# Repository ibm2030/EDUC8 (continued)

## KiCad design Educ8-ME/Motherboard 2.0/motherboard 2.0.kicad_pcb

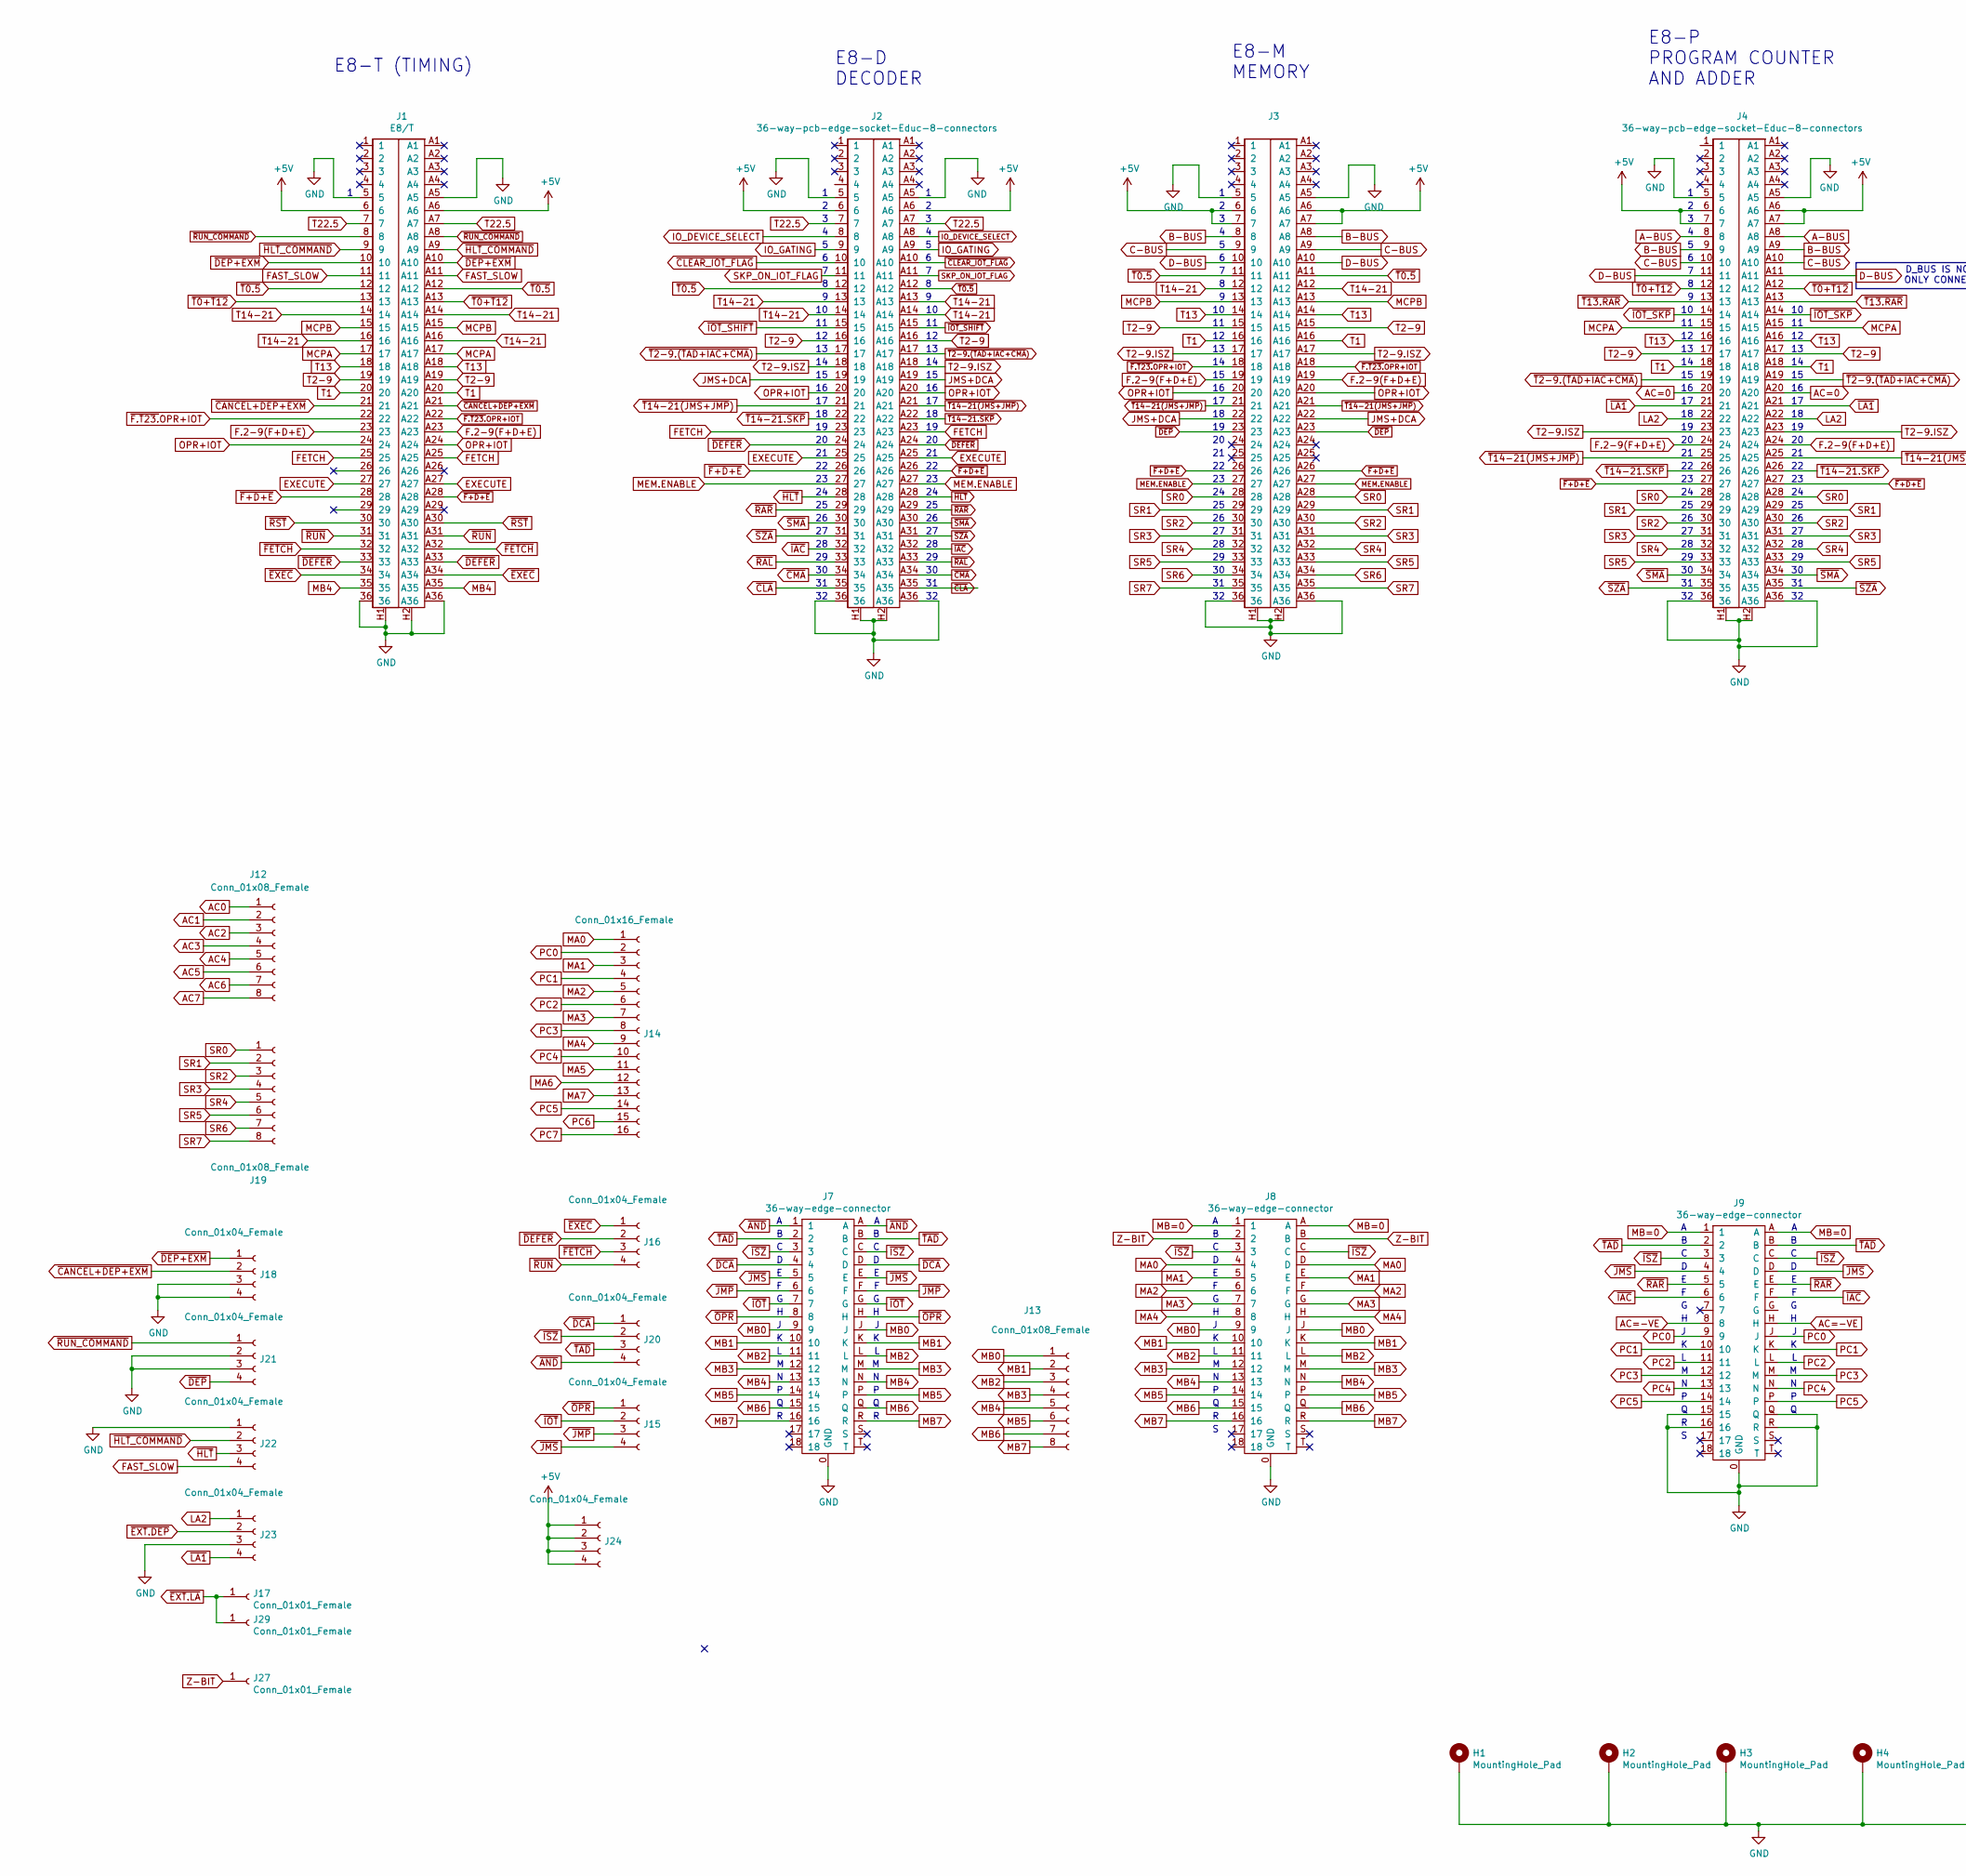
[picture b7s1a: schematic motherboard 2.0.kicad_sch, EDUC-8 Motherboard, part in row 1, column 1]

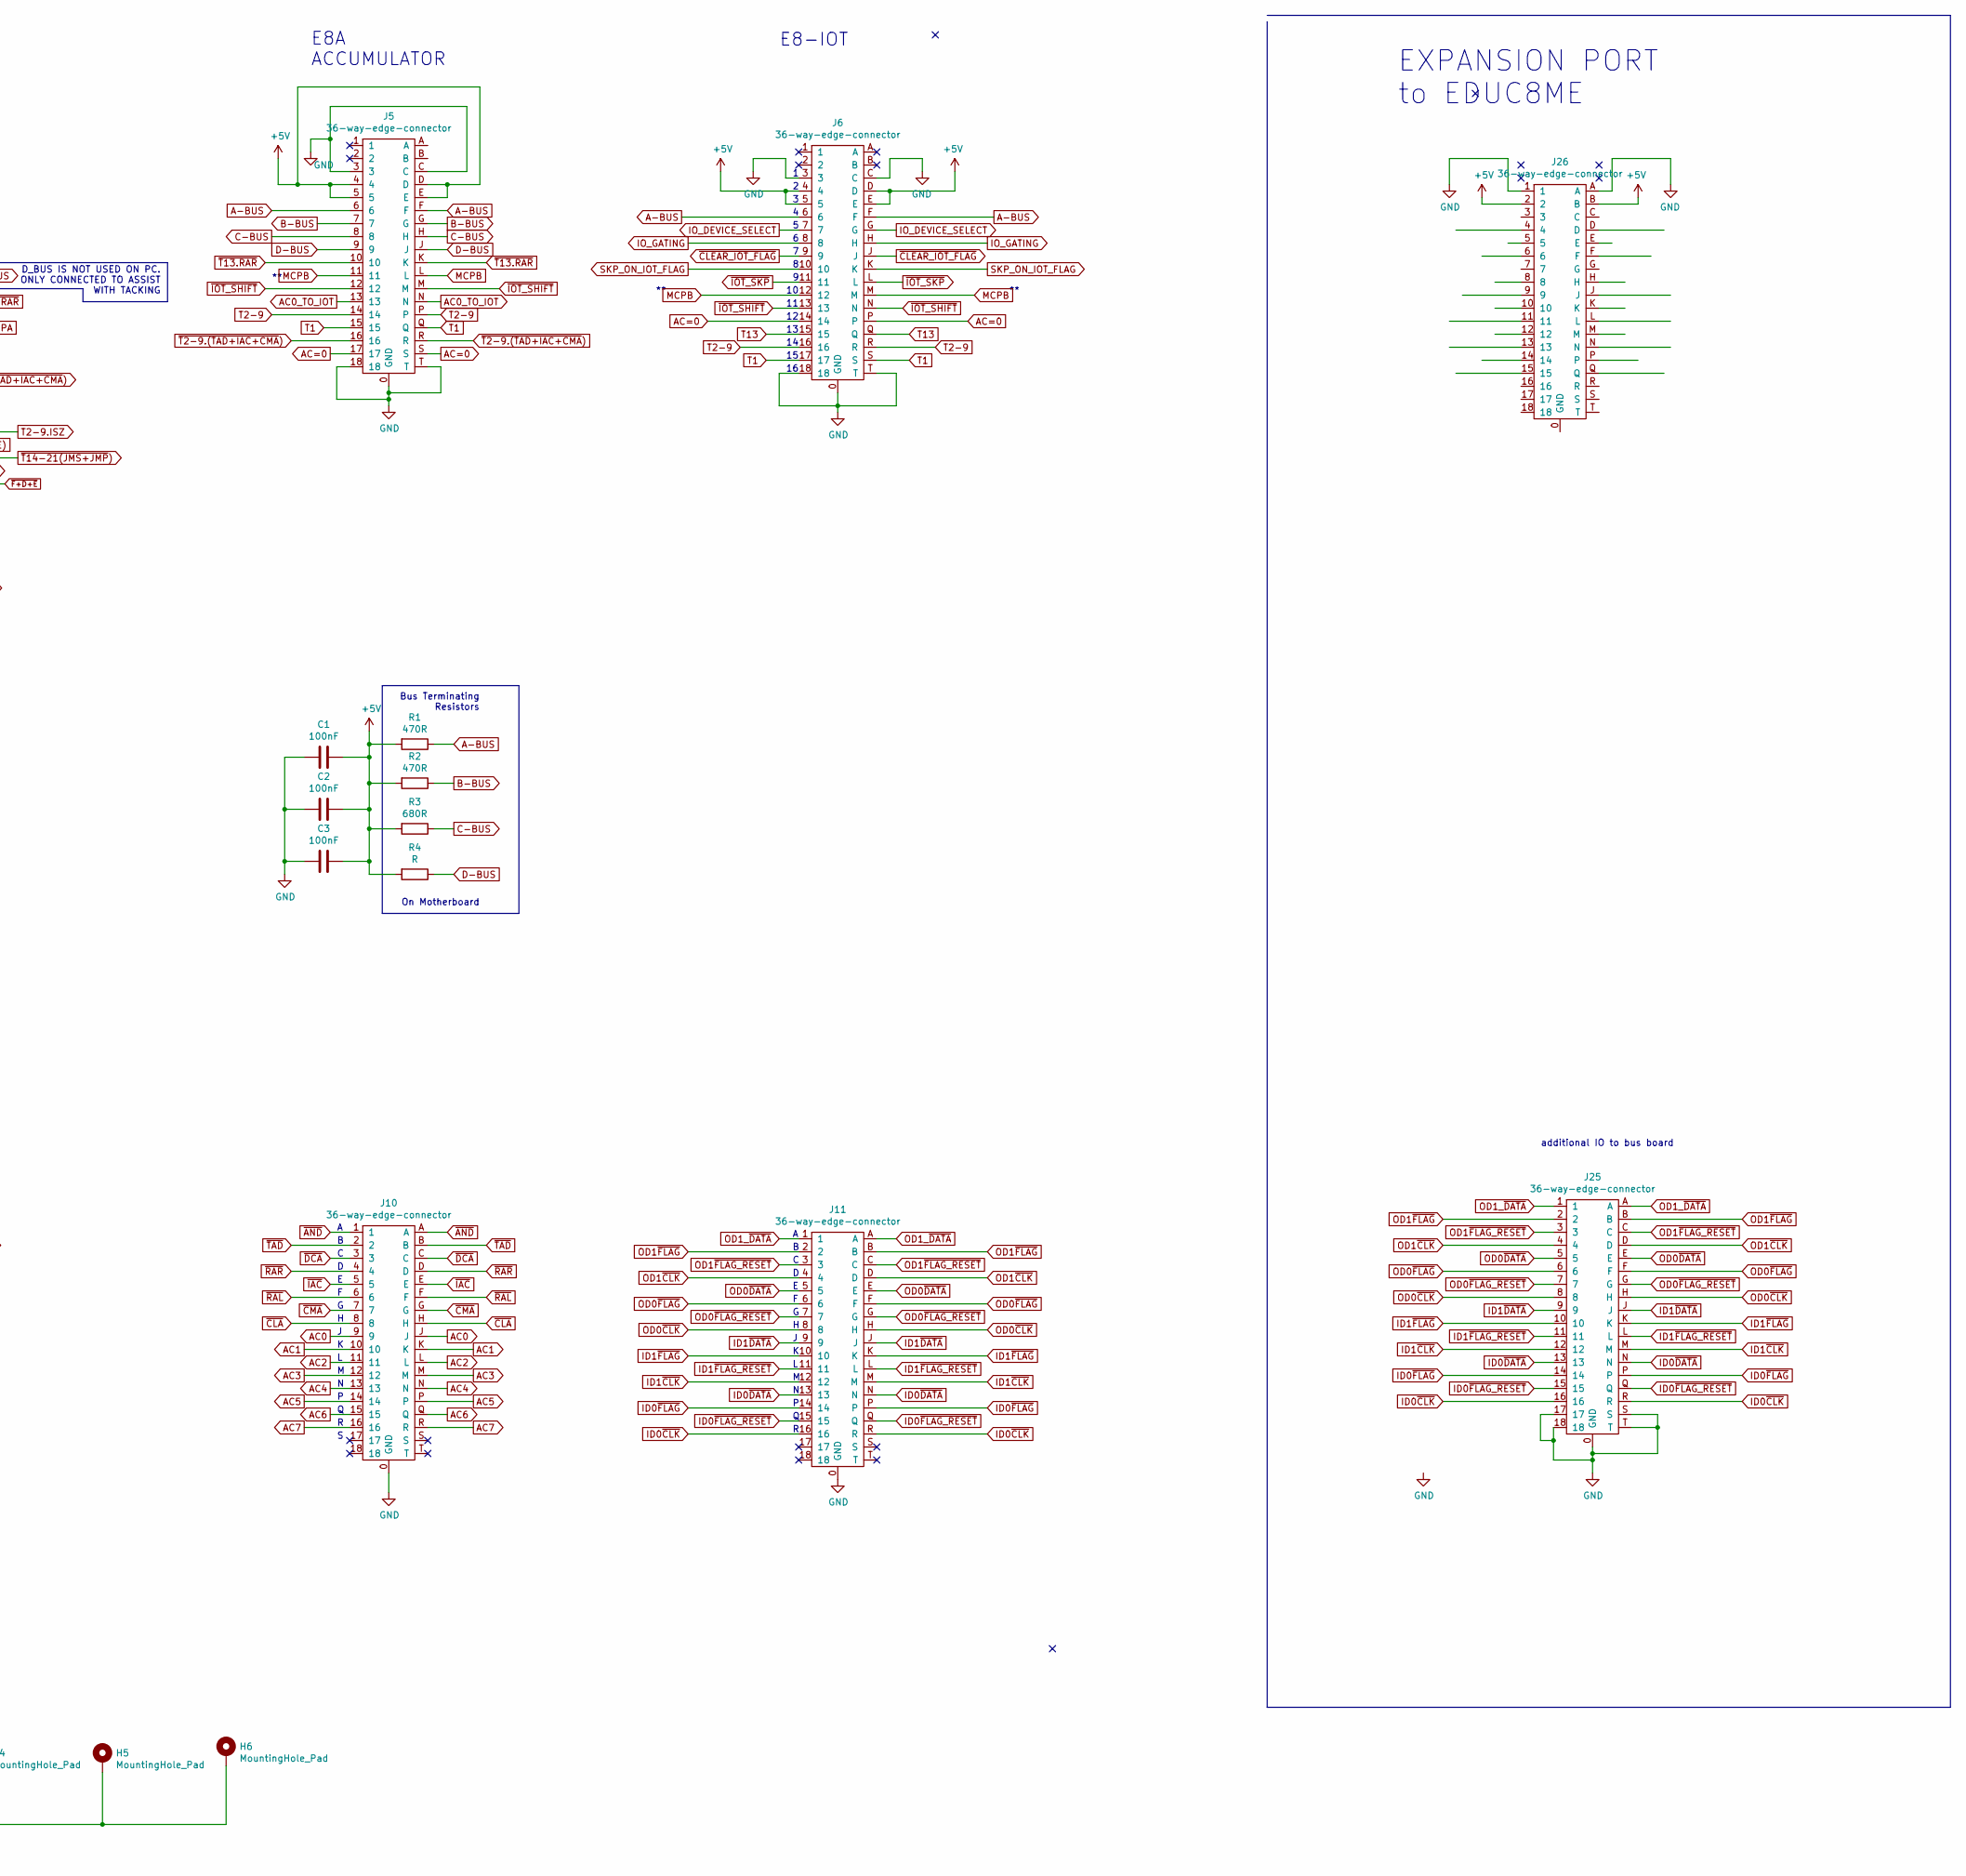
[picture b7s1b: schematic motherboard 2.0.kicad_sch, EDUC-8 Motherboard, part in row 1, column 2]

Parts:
C1, C2, C3: 100nF; C_Disc_D8.0mm_W5.0mm_P7.50mm
H1, H2, H3, H4, H5, H6: MountingHole_Pad; MountingHole_3.2mm_M3_Pad_Via
J1: E8/T; 72_way_3.96mm_card_edge_socket
J2, J4: 36-way-pcb-edge-socket-Educ-8-connectors; 72_way_3.96mm_card_edge_socket
J3: (no value)
J5, J6, J7, J8, J9, J10, J11, J25, J26: 36-way-edge-connector; 36_way_3.96mm_card_edge_socket
J12, J13, J19: Conn_01x08_Female; PinHeader_1x08_P2.54mm_Vertical
J14: Conn_01x16_Female; PinHeader_1x16_P2.54mm_Vertical
J15, J16, J18, J20, J21, J22, J23, J24: Conn_01x04_Female; PinHeader_1x04_P2.54mm_Vertical
J17, J27, J29: Conn_01x01_Female; PinHeader_1x01_P2.54mm_Vertical
R1, R2: 470R; R_Axial_DIN0207_L6.3mm_D2.5mm_P10.16mm_Horizontal
R3: 680R; R_Axial_DIN0207_L6.3mm_D2.5mm_P10.16mm_Horizontal
R4: R; R_Axial_DIN0207_L6.3mm_D2.5mm_P10.16mm_Horizontal

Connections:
+5V: C1.1, C2.1, C3.1, J1.6, J1.A6, J2.6, J2.A6, J3.6, J3.7, J3.A6, J3.A7, J4.6, J4.7, J4.A6, J4.A7, J5.4, J5.5, J5.D, J5.E, J6.4, J6.5, J6.D, J6.E, J24.1, J24.2, J24.3, J24.4, J26.2, J26.B, R1.2, R2.2, R3.2, R4.2
A-BUS: J4.8, J4.A8, J5.6, J5.F, J6.6, J6.F, R1.1
AC0: J10.9, J10.J, J12.1
AC0_TO_IOT: J5.13, J5.N
AC1: J10.10, J10.K, J12.2
AC2: J10.11, J10.L, J12.3
AC3: J10.12, J10.M, J12.4
AC4: J10.13, J10.N, J12.5
AC5: J10.14, J10.P, J12.6
AC6: J10.15, J10.Q, J12.7
AC7: J10.16, J10.R, J12.8
AC=0: J4.20, J4.A20, J5.17, J5.S, J6.14, J6.P
AC=-VE: J9.8, J9.H
B-BUS: J3.8, J3.A8, J4.9, J4.A9, J5.7, J5.G, R2.1
C-BUS: J3.9, J3.A9, J4.10, J4.A10, J5.8, J5.H, R3.1
D-BUS: J3.10, J3.A10, J4.11, J4.A11, J5.9, J5.J, R4.1
EXECUTE: J1.27, J1.A27, J2.25, J2.A25
F.2-9(F+D+E): J1.23, J1.A23, J3.19, J3.A19, J4.24, J4.A24
FAST_SLOW: J1.11, J1.A11, J22.4
FETCH: J1.25, J1.A25, J2.23, J2.A23
GND: C1.2, C2.2, C3.2, H1.1, H2.1, H3.1, H4.1, H5.1, H6.1, J1.5, J1.36, J1.A5, J1.A36, J1.H1, J1.H2, J2.5, J2.36, J2.A5, J2.A36, J2.H1, J2.H2, J3.5, J3.36, J3.A5, J3.A36, J3.H1, J3.H2, J4.5, J4.36, J4.A5, J4.A36, J4.H1, J4.H2, J5.0 (GND), J5.3, J5.18, J5.C, J5.T, J6.0 (GND), J6.3, J6.18, J6.C, J6.T, J7.0 (GND), J8.0 (GND), J9.0 (GND), J9.15, J9.16, J9.Q, J9.R, J10.0 (GND), J11.0 (GND), J18.3, J18.4, J21.2, J21.3, J22.1, J23.3, J25.0 (GND), J25.17, J25.18, J25.S, J25.T, J26.1, J26.A
ID0~CLK: J11.16, J11.R, J25.16, J25.R
ID0~DATA: J11.13, J11.N, J25.13, J25.N
ID0~FLAG_RESET: J11.15, J11.Q, J25.15, J25.Q
ID0~FLAG: J11.14, J11.P, J25.14, J25.P
ID1~CLK: J11.12, J11.M, J25.12, J25.M
ID1~DATA: J11.9, J11.J, J25.9, J25.J
ID1~FLAG_RESET: J11.11, J11.L, J25.11, J25.L
ID1~FLAG: J11.10, J11.K, J25.10, J25.K
IO_DEVICE_SELECT: J2.8, J2.A8, J6.7, J6.G
IO_GATING: J2.9, J2.A9, J6.8, J6.H
JMS+DCA: J2.19, J2.A19, J3.22, J3.A22
LA2: J4.22, J4.A22, J23.1
MA0: J8.4, J8.D, J14.1
MA1: J8.5, J8.E, J14.3
MA2: J8.6, J8.F, J14.5
MA3: J8.7, J8.G, J14.7
MA4: J8.8, J8.H, J14.9
MA5: J14.11
MA6: J14.12
MA7: J14.13
MB0: J7.9, J7.J, J8.9, J8.J, J13.1
MB1: J7.10, J7.K, J8.10, J8.K, J13.2
MB2: J7.11, J7.L, J8.11, J8.L, J13.3
MB3: J7.12, J7.M, J8.12, J8.M, J13.4
MB4: J1.35, J1.A35, J7.13, J7.N, J8.13, J8.N, J13.5
MB5: J7.14, J7.P, J8.14, J8.P, J13.6
MB6: J7.15, J7.Q, J8.15, J8.Q, J13.7
MB7: J7.16, J7.R, J8.16, J8.R, J13.8
MB=0: J8.1, J8.A, J9.1, J9.A
MCPA: J1.17, J1.A17, J4.15, J4.A15
MCPB: J1.15, J1.A15, J3.13, J3.A13, J5.11, J5.L, J6.12, J6.M
MEM.ENABLE: J2.27, J2.A27, J3.27, J3.A27
OD0~CLK: J11.8, J11.H, J25.8, J25.H
OD0~DATA: J11.5, J11.E, J25.5, J25.E
OD0~FLAG_RESET: J11.7, J11.G, J25.7, J25.G
OD0~FLAG: J11.6, J11.F, J25.6, J25.F
OD1_~DATA: J11.1, J11.A, J25.1, J25.A
OD1~CLK: J11.4, J11.D, J25.4, J25.D
OD1~FLAG_RESET: J11.3, J11.C, J25.3, J25.C
OD1~FLAG: J11.2, J11.B, J25.2, J25.B
OPR+IOT: J1.24, J1.A24, J2.20, J2.A20, J3.20, J3.A20
PC0: J9.9, J9.J, J14.2
PC1: J9.10, J9.K, J14.4
PC2: J9.11, J9.L, J14.6
PC3: J9.12, J9.M, J14.8
PC4: J9.13, J9.N, J14.10
PC5: J9.14, J9.P, J14.14
PC6: J14.15
PC7: J14.16
SKP_ON_IOT_FLAG: J2.11, J2.A11, J6.10, J6.K
SR0: J3.28, J3.A28, J4.28, J4.A28, J19.1
SR1: J3.29, J3.A29, J4.29, J4.A29, J19.2
SR2: J3.30, J3.A30, J4.30, J4.A30, J19.3
SR3: J3.31, J3.A31, J4.31, J4.A31, J19.4
SR4: J3.32, J3.A32, J4.32, J4.A32, J19.5
SR5: J3.33, J3.A33, J4.33, J4.A33, J19.6
SR6: J3.34, J3.A34, J19.7
SR7: J3.35, J3.A35, J19.8
T1: J1.20, J1.A20, J3.16, J3.A16, J4.18, J4.A18, J5.15, J5.Q, J6.17, J6.S
T2-9: J1.19, J1.A19, J2.16, J2.A16, J3.15, J3.A15, J4.17, J4.A17, J5.14, J5.P, J6.16, J6.R
T2-9.ISZ: J2.18, J2.A18, J3.17, J3.A17, J4.23, J4.A23
T13: J1.18, J1.A18, J3.14, J3.A14, J4.16, J4.A16, J6.15, J6.Q
T14-21: J1.14, J1.16, J1.A14, J1.A16, J2.13, J2.14, J2.A13, J2.A14, J3.12, J3.A12
T22.5: J1.7, J1.A7, J2.7, J2.A7
Z-BIT: J8.2, J8.B, J27.1
~AND: J7.1, J7.A, J10.1, J10.A, J20.4
~CANCEL+DEP+EXM: J1.21, J1.A21, J18.2
~CLA: J2.35, J2.A35, J10.8, J10.H
~CLEAR_IOT_FLAG: J2.10, J2.A10, J6.9, J6.J
~CMA: J2.34, J2.A34, J10.7, J10.G
~DCA: J7.4, J7.D, J10.3, J10.C, J20.1
~DEFER: J1.33, J1.A33, J2.24, J2.A24, J16.2
~DEP+EXM: J1.10, J1.A10, J18.1
~DEP: J3.23, J3.A23, J21.4
~EXEC: J1.34, J1.A34, J16.1
~EXT.DEP: J23.2
~EXT.LA: J17.1, J29.1
~F+D+E: J1.28, J1.A28, J2.26, J2.A26, J3.26, J3.A26, J4.27, J4.A27
~F.T23.OPR+IOT: J1.22, J1.A22, J3.18, J3.A18
~FETCH: J1.32, J1.A32, J16.3
~HLT_COMMAND: J1.9, J1.A9, J22.2
~HLT: J2.28, J2.A28, J22.3
~IAC: J2.32, J2.A32, J9.6, J9.F, J10.5, J10.E
~IOT_SHIFT: J2.15, J2.A15, J5.12, J5.M, J6.13, J6.N
~IOT_SKP: J4.14, J4.A14, J6.11, J6.L
~IOT: J7.7, J7.G, J15.2
~ISZ: J7.3, J7.C, J8.3, J8.C, J9.3, J9.C, J20.2
~JMP: J7.6, J7.F, J15.3
~JMS: J7.5, J7.E, J9.4, J9.D, J15.4
~LA1: J4.21, J4.A21, J23.4
~OPR: J7.8, J7.H, J15.1
~RAL: J2.33, J2.A33, J10.6, J10.F
~RAR: J2.29, J2.A29, J9.5, J9.E, J10.4, J10.D
~RST: J1.30, J1.A30
~RUN_COMMAND: J1.8, J1.A8, J21.1
~RUN: J1.31, J1.A31, J16.4
~SMA: J2.30, J2.A30, J4.34, J4.A34
~SZA: J2.31, J2.A31, J4.35, J4.A35
~T0+T12: J1.13, J1.A13, J4.12, J4.A12
~T0.5: J1.12, J1.A12, J2.12, J2.A12, J3.11, J3.A11
~T2-9.(TAD+IAC+CMA): J2.17, J2.A17, J4.19, J4.A19, J5.16, J5.R
~T13.RAR: J4.13, J4.A13, J5.10, J5.K
~T14-21(JMS+JMP): J2.21, J2.A21, J3.21, J3.A21, J4.25, J4.A25
~T14-21.SKP: J2.22, J2.A22, J4.26, J4.A26
~TAD: J7.2, J7.B, J9.2, J9.B, J10.2, J10.B, J20.3

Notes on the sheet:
E8-P PROGRAM COUNTER AND ADDER
EXPANSION PORT to EDUC8ME
E8A ACCUMULATOR
additional IO to bus board
E8-M MEMORY
E8-T (TIMING)
On Motherboard
Bus Terminating Resistors
D_BUS IS NOT USED ON PC. ONLY CONNECTED TO ASSIST WITH TACKING
E8-D DECODER
E8-IOT

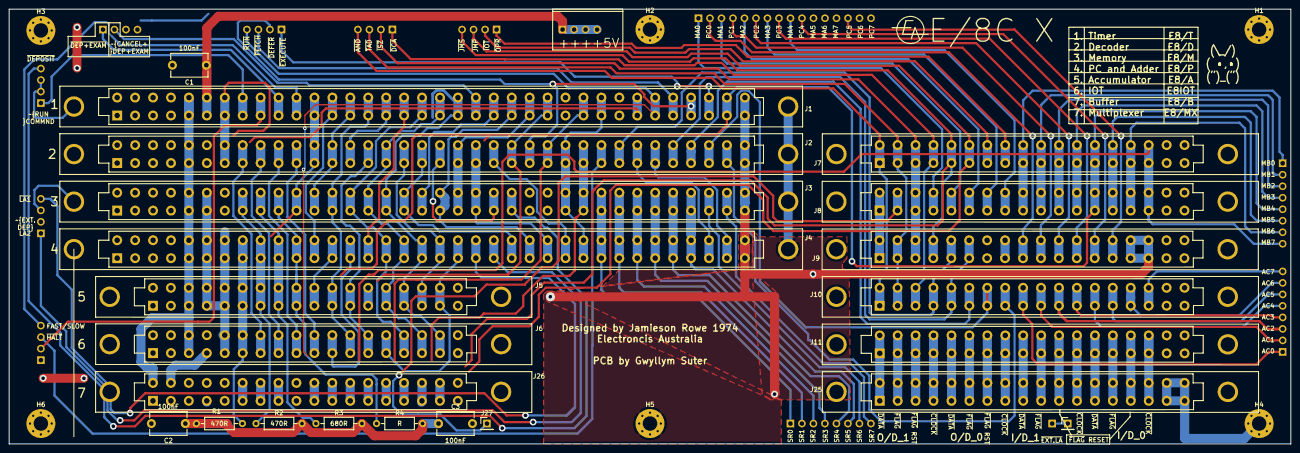
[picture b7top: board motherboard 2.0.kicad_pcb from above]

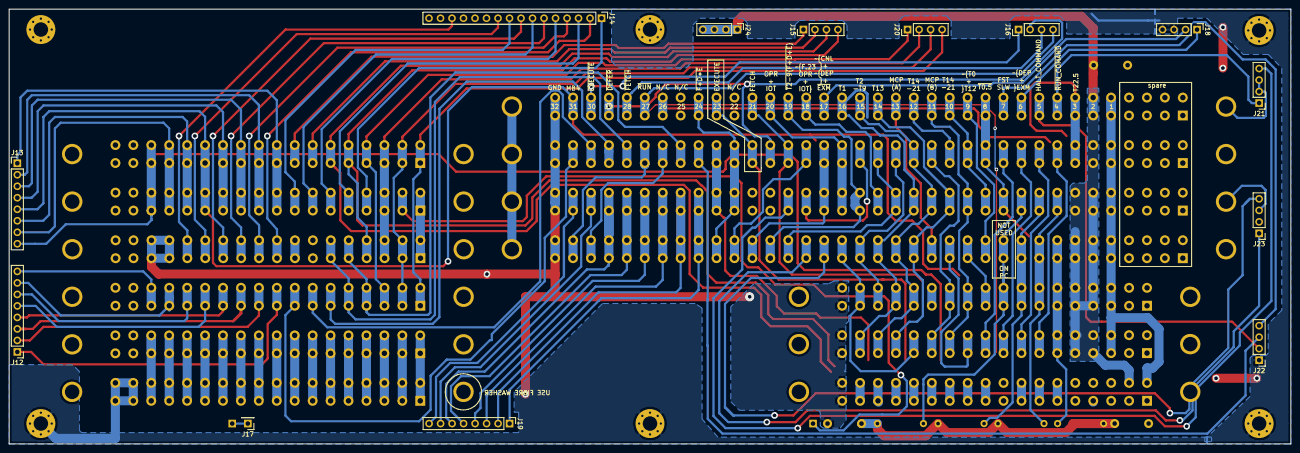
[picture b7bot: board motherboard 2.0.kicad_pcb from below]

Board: 2 copper layers, 283.0 x 96.0 mm, 41 parts (13 on the bottom side), 120 nets.
